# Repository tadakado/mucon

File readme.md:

# 使用上の注意

1. USB-SWDボードを接続する際は、必ず、電源スイッチをオフにして電池を外してください。電源スイッチをオフにしないと 3.3VがBLEモジュール(MDBT50Q)に接続されません。また、ボード間の"V"と"B"の印刷が対応するように接続してください。
2. BLE Micro Pro用に公開されている下記ファームウェアを、独自に書き込んでいます。本キーボードに関して、BLE Micro Pro作者のせきごんさんには問い合わせをしないでください。
    * [BLE Micro Pro Bootloader](https://github.com/sekigon-gonnoc/BLE-Micro-Pro)
    * [QMK for BMP](https://github.com/sekigon-gonnoc/qmk_firmware)
3. キーボード本体右上の穴はキーホルダー用の穴です。ショートの恐れがあるため、金属製リングの使用は避けてください。携帯ストラップなどに使われる紐がお勧めです。同梱のスペーサは携帯ストラップの紐を通す際に、本体、スペーサ、ケースの順に通してください。紐によってケース変形してキーが誤動作するのを防止します。無くしやすいので気をつけてください。

# はじめに

μ'con(もしくはmucon)はキーが5個の5%キーボードです。BLEによるデバイスのメディア操作(音量や再生/停止など)用に設計されています。キーボード本体(メインボード)と各種設定に用いるUSB-SWDボードから成ります。USBはType-Cです。電池はCR2032を使い、BLE Micro Proのファームウェアで、6ヶ月以上動作します。本体重量約4g(電池含まず)。μ'conの名前は、music controller、micro(μ) controller/computer、そしてあるアーティストに由来しています。

# 同梱物

* 本体 x 1個
* USB-SWDボード x 1個
* コンスルー(7pin) x 1個
* TPUケース x 2個
* スペーサ(CT-2002) x 2個 (ストラップをつける際に使用します)

# 初期設定(シンプル)

出荷時の状態から、電池を入れて電源スイッチをオンにすると一台目をペアリングすることができます。
(初期設定(通常)の5.までを実行するとペアリング済みデバイスが消去され出荷時相当になります)

# 初期設定(通常)

1. 電源スイッチをオフにして、つまようじ等で電池を外し、USB-SWDボードを接続して、PC/Macに接続してください。
    * USB-SWDボードの接続は、1.27mmピッチのコンスルーを用います。メインボード上の"V"と"B"の印刷と、USB-SWDボード上の"V"と"B"の印刷が対応するように接続してください。"V"と"B"は、VCCとVBUSのため、逆に接続すると、想定外の電圧がかかり破損の原因となります。
    * 電池ホルダとのショートに気を付けてください。ショート防止のため、USB-SWDボードの裏には絶縁テープが貼ってあります。
    * 

2. PC/MacにUSBケーブルで接続してください。
    * PCの場合、Tera Termで、COM??ポート(ポート番号??はマシンによって異なる)に接続してください。
    * Macの場合、ターミナルで`screen /dev/tty.usbmodem??`を実行します。終了する際は`ctrl-a k`です。
3. BLE Micro ProのCLIのコマンドを使い初期設定をします。
    * `help`コマンドで、BLE Micro ProのCLIのコマンド一覧が出ます。
4. `show`コマンドでペアリング済みのデバイスの一覧が出ます。ペアリング済みのデバイスがある場合は、`del`コマンドで消去してください。
5. デバイス側のペアリング情報も消してください。
6. `adv`コマンドでアドバタイズを開始してください。デバイス側に(BMP)muconが出たらペアリングをしてください。
    * 二台目をペアリングする際は、一台目のデバイスのBlueetoohをオフにしてから、`adv`コマンドを再実行してください。
7. ペアリングが完了したら、USB-SWDボードを取り外し、電池を入れて、電源スイッチをオンにしてください。

# 使用方法

1. 電源スイッチをオンにするとLEDが(電池容量に応じて)1～3回点滅します。最後に少し長く点滅したら接続完了です。
2. キーSWは、左上から反時計回りにSW1～SW5です。
    ```
    SW1   O
    SW2  SW5
    SW3  SW4
    ```
3. デフォルトの設定では、SW1を押しながらSW2を押すと一台目のデバイス、SW1を押しながらSW3を押すと二台目のデバイスに再接続します。
4. SW2が再生/停止、SW3が音量下げる、SW4が音量上げる、SW5は、一回押しが次の曲、二回押しが前の曲です。

# 設定の変更

1. Macでストレージとして認識しない場合(macOS Sonoma以降)は、[シェルスクリプト](macOS/mucon_mount.sh)を使ってマウントしてください。ターミナルで`./mucon_mount.sh mount`を実行します。
2. BLE Micro Proの[ドキュメント](https://sekigon-gonnoc.github.io/BLE-Micro-Pro/#/edit_keymap_file)に従い、
"KEYMAP.JSN"の`"layers":[`の後ろを編集してください。 
3. 設定を変更する際は、PC/Mac上に"KEYMAP.JSN"をコピーして編集後に"mucon"ドライブに戻して(コピーして)ください。
4. 動作がおかしいときは
    * 正しくコピーされているか確認してみてください。ファイルを開いてみるほかに、CLIの`map`コマンドでも確認できます。二回コピーするとうまくいく場合もあります。
    * ファイルの記述にミスがある場合ファイルが正しくコピーされません。デフォルトの"KEYMAP.JSN"でコピーできるか確認してみてください。
    * BLE Micro ProのCLIのコマンド`del`および、デバイス側のペアリング情報を消して、初期設定をしてみてください。
5. ファームウェアのアップデートは、どのような影響があるかわからないため、案内がある場合を除いて行わないでください。
    * アップデートの際は、CLIの`dfu`コマンドにより、dfuモードに移行します。uf2ファイルをドライブにコピーするとアップデートが行われます。
    * また、USBを用いずにSWDでファームウェアを書き込むこともできます。(上級者向け)
    * 書き込んであるファームは、[BLE Micro Pro Bootloader v0.11.0](https://github.com/sekigon-gonnoc/BLE-Micro-Pro/releases/download/v0.11.0/ble_micro_pro_bootloader_0_11_0.uf2)と[QMK for BMP v0.11.2](https://github.com/sekigon-gonnoc/qmk_firmware/releases/download/bmp-0.11.2/ble_micro_pro_default_0_11_2_1.uf2)です。
    * 実験的に[専用ファームウェア](firmware)を用意しました。LEDで接続接続デバイスを確認したり、Musicモードとプレゼンテーションモードを切り替えたりできます。

# ハードウェア

1. 回路図は添付資料(pdfファイル)をご覧ください。"pcb"にはKicadの設計データがあります。
2. BLE Micro Proのファームウェアと、CircutPythonが動くように設計されています。CircuitPythonは消費電力が大きく、電池動作には向いていません。CircuitPythonに関しては資料を参照ください。
3. メインボードにはLEDのほかに、水晶発振子とWS2812C用のパターンがありますが搭載しておりません。水晶発振子はBLE Micro Proのファームウェアでは必須ではないため、また、WS2812Cは省電力化のため外してあります。
4. メインボード裏面には、テスト用のパッドがあります。中央寄りからBOOT, RESET, SWITCH, D2, GNDです。詳細は回路図を参照ください。
5. USB-SWDボードを接続する際は、電源スイッチをオフにして、必ず電池を外してください。電源スイッチをオフにしないと 3.3VがBLEモジュール(MDBT50Q)に接続されません。
6. USB-SWDボードにはUSBの5VからVCCの3.3Vを作るレギュレータがあります。また、μ'con接続用スルーホール(1x7 1.27mm)、SWD(2x5 1.27mm)ピンヘッダ、SWD用スルーホール(1x4 2.54mm)が二つあります。スルーホール径は0.8mm(設計値)です。
7. SWDピンヘッダには、J-LinkやBlack Magic Probeが接続できます。SWD用スルーホールは、ST-LinkV2やBluePill Black Magic Probeの接続用です。SWDによる書き込みは資料を参照ください。
8. BLE Micro Proのファームウェアはマトリックスキーボードを想定しているため、設定ファイルでは、使っていない端子を一つrow_pin(=6,P0.16)に割り当てています。
9. 配線の都合上、P0.05とP0.06がLEDに繋がっていますが、使用するのはP0.05のみです。
10. ケースの設計データ(Fusion360)は"case"にあります。

# デフォルトの設定ファイルの内容

"BMP_config"にファイルがあります。

KEYMAP.JSN
```
{"keyboard":"mucon",
"keymap":"",
"layout":"LAYOUT",
"layers":[
    ["MO(1)", "KC_MPLY", "KC_VOLD","KC_VOLU", "EX(TDD(KC_MNXT,KC_MPRV))"],
    ["KC_TRANS", "ADV_ID0", "ADV_ID1", "KC_NO", "KC_NO"]
]}
```
CONFIG.JSN (編集しない)
```
{"config":{
    "version":2,
    "device_info":{"vid":"0xcafe","pid":"0x9001",
        "name":"mucon","manufacture":"tadakado","description":"A music controller with 5 buttons"},
    "matrix":{"rows":1,"cols":5,"device_rows":1,"device_cols":5,
         "debounce":1,"is_left_hand":1,"diode_direction":0,
         "row_pins":[6],
         "col_pins":[16, 15, 18, 7, 9],
    "layout":[1, 2, 3, 4, 5]},
    "mode":"SINGLE","startup":1,
    "peripheral":{"max_interval":200,"min_interval":100,"slave_latency":0},
    "central":{"max_interval":200,"min_interval":100,"slave_latency":0},
    "led":{"pin":1, "num":1},
    "keymap":{"locale":"JP","use_ascii":0},
    "reserved":[0,20,0,0,0,0,0,0]
}}
```
TAPTERM (編集しない)
```
{"tapping_term":{
	"KC_NO":500
}}
```

# BLE Micro ProのCLI

ドキュメントにはすべてのコマンドの説明が書かれていないようです。CLIの[コード](https://github.com/sekigon-gonnoc/qmk_firmware/blob/dev/ble_micro_pro/tmk_core/protocol/nrf/sdk15/cli.c)やAPIの[コード](https://github.com/sekigon-gonnoc/qmk_firmware/blob/dev/ble_micro_pro/tmk_core/protocol/nrf/sdk15/apidef.h)を参照ください。

# ケース

"case"にFusion360の設計ファイルおよび、3Dプリンタで印刷に用いるstlファイルがあります。TPUでの印刷を想定しています。

# SWDでファームウェアの書き込み方法

(確実なのはJ-Link、安価なのはST-Link V2またはBluePill)

* USBとSWDの両方を接続してください。USBはVCCの3.3Vを作るために使用します。
* J-Linkを用いる場合は、[nRF Connect for Desktop](https://www.nordicsemi.com/Products/Development-tools/nRF-Connect-for-desktop)からProgrammerを起動するとhexファイルが書き込めます。
* Black Magic Probeまたは、BluePill Black Magic Probeを用いる場合は、gdbからhexファイルが書き込めます。
* ST-Link V2を用いる場合には、OpenOCDからhexファイルが書き込めます。
* J-LinkやBlack Magic Probeで使用するSWD(2x5 1.27mm)ピンヘッダを実装しています。ST-Link V2やBluePillを使用する場合は、SWD用スルーホールにピンヘッダを実装して使用してください。干渉を防ぐため、外側のスルーホールを使うことをお勧めします。

## ST-Link V2による書き込み

### ST-Link V2購入先
* [SZ Aitexm Store](https://www.aliexpress.com/item/32792513237.html)、
[Shigezone](https://www.shigezone.com/product/st-link/)

### ST-Link V2をWindows10に認識させる
1. [Zadig](https://zadig.akeo.ie)をダウンロードして実行
2. STM32 STLink => WinUSB

## ST-Link V2とOpenOCDによるNRF52への書き込み
* [参考情報1](https://kunsen.net/2018/09/30/post-1784/)
* [参考情報2](https://4k2.de/microcontroller/openocd-flashing-nrf52/)
1. ソフトのダウンロード
    * [OpenOCD](https://github.com/openocd-org/openocd/releases/download/v0.11.0/openocd-v0.11.0-i686-w64-mingw32.tar.gz)
2. 書き込み
    1. 方法1 コマンドライン
        ```
        bin¥openocd -s share/openocd/scripts -f interface/stlink-v2.cfg -f target/nrf52.cfg -c init -c "reset init" -c halt -c "nrf5 mass_erase" -c “program firmware.hex verify” -c reset -c exit
        ```
    2. 方法2 サーバを起動
        ```
        bin¥openocd -s share/openocd/scripts -f interface/stlink-v2.cfg -f target/nrf52.cfg
        ```
        localhost:4444 にアクセス
        ```
        init
        reset init
        halt
        nrf5 mass_erase
        program firmware.hex verify
        reset
        exit
        ```

## Black Magic Probeによる書き込み

### Black Magic ProbeとgdbによるNRF52への書き込み
* [参考情報1](https://devzone.nordicsemi.com/nordic/nordic-blog/b/blog/posts/flashing-and-debugging-nrf5152-with-a-cheap-blackm)
* [参考情報2](https://developer.arm.com/tools-and-software/open-source-software/developer-tools/gnu-toolchain/downloads-1)
* COMの番号は二つあるうちの一つ目を使う。
* COM番号が大きいとうまく動かないことがあるため、デバイスマネージャーで、表示>表示デバイスの表示として、デバイスのアンインストールで不要なものを削除
    ```
    arm-none-eabi-gdb.exe
    target extended-remote COM4
    monitor swdp_scan
    attach 1
    (monitor erase_mass)
    load firmware.hex
    ```

### Balck Magic Probeとして使えるBluePill Black Magic Probeの作り方(要 ST-Link V2 & BluePill)
* [参考情報](https://jeelabs.org/202x/bmp/)
1. ソフトとデータをダウンロード
    * [ST-Link](https://github.com/stlink-org/stlink/releases/download/v1.7.0/stlink-1.7.0-x86_64-w64-mingw32.zip)
    * [Black Magic Probe](https://github.com/blackmagic-debug/blackmagic/releases/download/v1.7.1/v1.7.1.tar.gz)
2. 必要なファイルをまとめる
    * blackmagic_dfu-swlink.bin
    * blackmagic-swlink.bin
    * st-flash.exe
3. 書き込み
    ```
    st-flash --reset write blackmagic_dfu-swlink.bin 0x8000000
    st-flash --flash=128k write blackmagic-swlink.bin 0x8002000
    ```
* その他の情報
    * Firmwareのスリム化 [参考情報](https://primalcortex.wordpress.com/2017/06/13/building-a-black-magic-debug-probe/)

# BLE Mirco Proファームウェア(uf2)からhexファイルへの変換方法

[参考情報](https://discord.com/channels/376937950409392130/508485002170990602/800355123637125170)

build_BMP_hex.sh
```
#!/bin/sh

mkdir build
cd build

curl -O -L https://github.com/sekigon-gonnoc/BLE-Micro-Pro/releases/download/v0.11.0/ble_micro_pro_bootloader_0_11_0.uf2
curl -O -L https://www.nordicsemi.com/-/media/Software-and-other-downloads/SoftDevices/S140/s140nrf52600.zip
unzip s140nrf52600.zip s140_nrf52_6.0.0_softdevice.hex
curl -O -L https://raw.githubusercontent.com/microsoft/uf2/a690c5a4d9abe393496b3ade88489d39da07b458/utils/uf2conv.py
curl -O -L https://raw.githubusercontent.com/microsoft/uf2/a690c5a4d9abe393496b3ade88489d39da07b458/utils/uf2families.json

dd if=ble_micro_pro_bootloader_0_11_0.uf2 of=BOOTLOADER.uf2 bs=1 count=242688
dd if=ble_micro_pro_bootloader_0_11_0.uf2 of=UICR.uf2 bs=1 skip=242688

python2 uf2conv.py -c -b 0xE0000 -o BOOTLOADER.bin BOOTLOADER.uf2
python2 uf2conv.py -c -b 0x10001000 -o UICR.bin UICR.uf2
objcopy --adjust-vma 0xE0000 -I binary -O ihex BOOTLOADER.bin BOOTLOADER.hex
objcopy --adjust-vma 0x10001000 -I binary -O ihex UICR.bin UICR.hex
```
REGOUT0を3.3Vにする設定(μ'conでは使わない)
```
cat > hex/UICR_REGOUT0_5_3v3.hex << EOF
:020000041000EA
:04130400FDFFFFFFEB
:00000001FF
EOF

unix2dos hex/UICR_REGOUT0_5_3v3.hex
```

# μ'con用CircuitPythonのビルド

"circuitpython"の下にAdafurit_nRF52_BootloaderとCircutPython向けのボード固有のコードがあります。

## Adafurit_nRF52_Bootloaderのビルド
コンパイル環境を構築したら、"circuitpython/boot"にあるファイルを"src/bords"の下に"mucon"を作成してコピーします。
```
make BOARD=mucon
```
で、コンパイルできます。"\_build/build-mucon"にある"\*\_s140\_\*.hex"と"*.uf2"が必要なバイナリです。

## CircuitPythonのビルド
コンパイル環境を構築したら、"circuitpython/ptyhnon"にあるファイルを"ports/nrf/boards"の下に"mucon"フォルダを作成してコピーします。
```
cd ports/nrf ; make V=2 BOARD=mucon
```
で、コンパイルできます。"build-mucon/firmware.uf2"が必要とするバイナリです。
クリスタル未搭載の場合には、"mpconfigboard.h" で`#define BOARD_HAS_32KHZ_XTAL (0)`を設定する必要があります。

### pyファイルのコンパイル(mpyの作成)
pythonのコードをそのまま保存するとサイズが大きくなるため、たくさんのライブラリを使う複雑なプログラムが組めません。そこでライブラリを含めてすべてのpyファイルをコンパイルして小さくします。
circuitpythonをインストールしたフォルダに、["tools/mpy_cross_all.py"](https://github.com/adafruit/circuitpython/blob/main/tools/mpy_cross_all.py)があります。例えば、"py/kmk"にコンパイルしたいpyファイルを置いて、以下を実行すると"mpy/kmk"の下にコンパイルされたmpyファイルができます。
```
python3 mpy_cross_all.py -o mpy/kmk py/kmk
```
なお、circuitpythonの標準ライブラリはmpyファイルとして提供されています。

### CircuitPythonでのCの利用
MicroPytnonにはmpyにCのコードをコンパイルしたバイナリを含めることができるますが、CircuitPythonではその機能は実装されていないため、カスタムモジュールを作りCircuitPython全体をコンパイルする必要があります。[参考情報](https://forums.adafruit.com/viewtopic.php?f=60&t=190383)

### KMKについて
CircuitPythonを利用したBLE HIDキーボードの実装が[KMK](https://github.com/KMKfw/kmk_firmware)です。CircuitPythonのBLE機能を利用しているため、機能が限定されます。また、CircuitPythonでは、スリープモードでの消費電力が大きいため、CRC2032が一日しか持ちません。これらの課題が解決すれば、開発環境として使えます。

# μ'con製造について
一つ一つ手作業で作成しています。Sn-Bi系の低融点ハンダを使用しているので、もし修理等をされる場合は半田ごてやヒートガンの温度設定に注意してください。リフローは160～180度、ヒートガンは160度、半田ごては270度(実測または設定値)で作業しています。

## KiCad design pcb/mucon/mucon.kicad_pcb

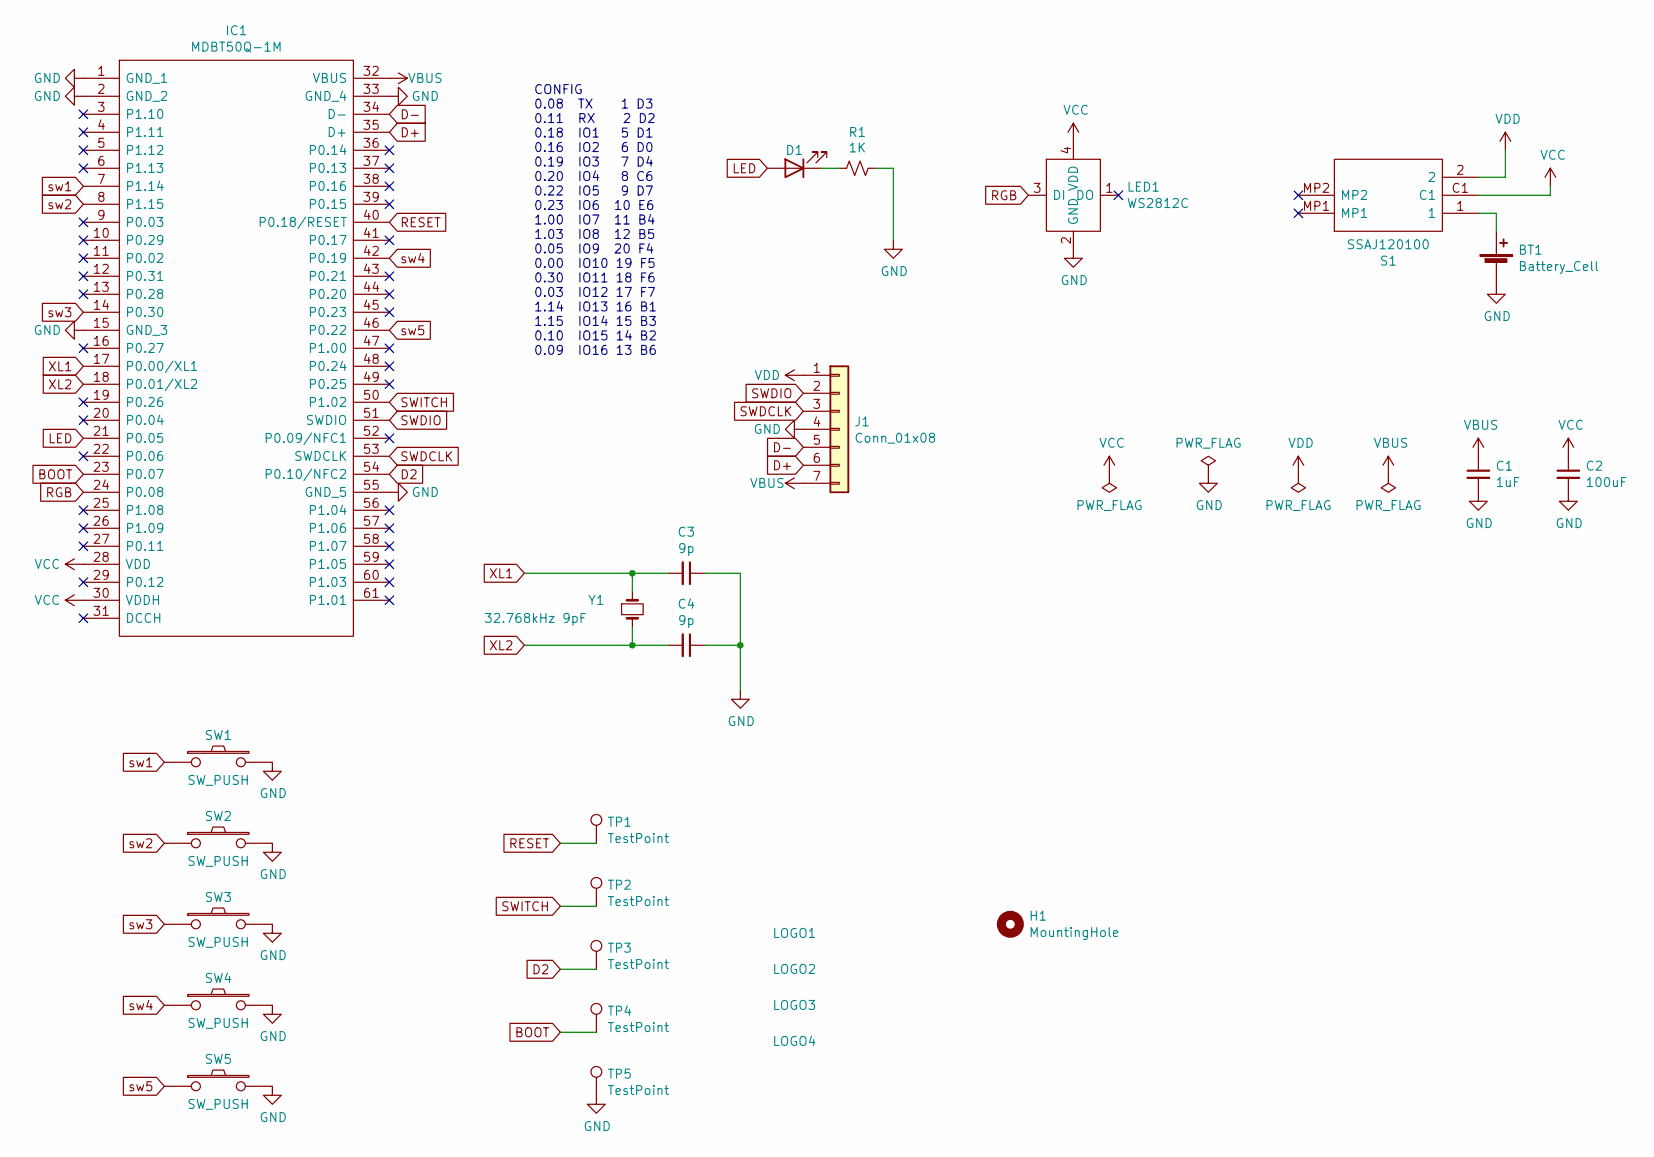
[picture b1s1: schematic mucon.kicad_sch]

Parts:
BT1: Battery_Cell; BK888_mod6
C1: 1uF; C_0603_1608Metric
C2: 100uF; C_1206_3216Metric
C3, C4: 9p; C_0402_1005Metric
D1: LED; LED_0603_1608Metric
H1: MountingHole; MountingHole_2.2mm_M2
IC1: MDBT50Q-1M; Manufacturer_Part_Number 113990582
J1: Conn_01x08; PinHeader_1x07_P1.27mm_Vertical
LED1: WS2812C; WS2812C2020; Manufacturer_Part_Number WS2812C-2020
LOGO1: Logo; mucon
LOGO2: Logo; mucon2
LOGO3: Logo; quarter_note3
LOGO4: Logo; star_3mm
R1: 1K; R_0603_1608Metric
S1: SSAJ120100; Manufacturer_Part_Number SSAJ120100
SW1, SW2, SW3, SW4, SW5: SW_PUSH; SKRPABE010
TP1, TP2, TP3, TP4, TP5: TestPoint; TestPoint_Pad_D1.0mm
Y1: 32.768kHz 9pF; CM9VT1A

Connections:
BOOT: IC1.23 (P0.07), TP4.1
D2: IC1.54 (P0.10/NFC2), TP3.1
D+: IC1.35 (D+), J1.6
D-: IC1.34 (D-), J1.5
GND: BT1.2 (-), C1.2, C2.2, C3.1, C4.1, IC1.1 (GND_1), IC1.2 (GND_2), IC1.15 (GND_3), IC1.33 (GND_4), IC1.55 (GND_5), J1.4, LED1.2 (GND), R1.1, SW1.2, SW2.2, SW3.2, SW4.2, SW5.2, TP5.1
LED: D1.2 (A), IC1.21 (P0.05)
unnamed: BT1.1 (+), S1.1
unnamed: D1.1 (K), R1.2
RESET: IC1.40 (P0.18/RESET), TP1.1
RGB: IC1.24 (P0.08), LED1.3 (DI)
SWDCLK: IC1.53 (SWDCLK), J1.3
SWDIO: IC1.51 (SWDIO), J1.2
SWITCH: IC1.50 (P1.02), TP2.1
VBUS: C1.1, IC1.32 (VBUS), J1.7
VCC: C2.1, IC1.28 (VDD), IC1.30 (VDDH), LED1.4 (VDD), S1.C1
VDD: J1.1, S1.2
XL1: C3.2, IC1.17 (P0.00/XL1), Y1.1
XL2: C4.2, IC1.18 (P0.01/XL2), Y1.2
sw1: IC1.7 (P1.14), SW1.1
sw2: IC1.8 (P1.15), SW2.1
sw3: IC1.14 (P0.30), SW3.1
sw4: IC1.42 (P0.19), SW4.1
sw5: IC1.46 (P0.22), SW5.1

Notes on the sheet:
CONFIG 0.08 TX 1 D3 0.11 RX 2 D2 0.18 IO1 5 D1 0.16 IO2 6 D0 0.19 IO3 7 D4 0.20 IO4 8 C6 0.22 IO5 9 D7 0.23 IO6 10 E6 1.00 IO7 11 B4 1.03 IO8 12 B5 0.05 IO9 20 F4 0.00 IO10 19 F5 0.30 IO11 18 F6 0.03 IO12 17 F7 1.14 IO13 16 B1 1.15 IO14 15 B3 0.10 IO15 14 B2 0.09 IO16 13 B6

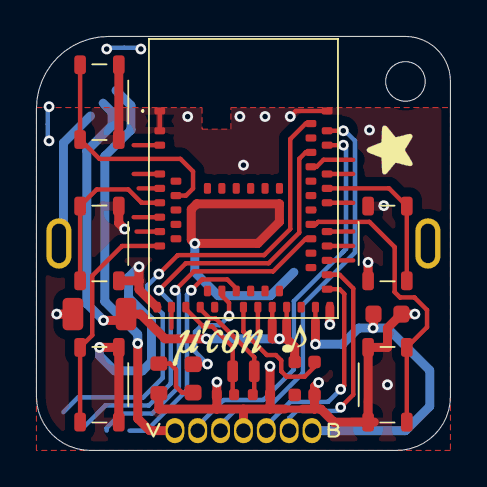
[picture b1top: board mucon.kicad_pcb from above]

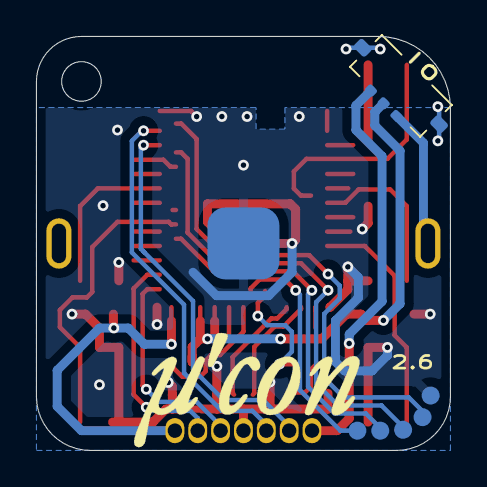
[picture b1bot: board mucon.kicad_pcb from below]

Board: 2 copper layers, 23.0 x 23.0 mm, 27 parts (8 on the bottom side), 23 nets.

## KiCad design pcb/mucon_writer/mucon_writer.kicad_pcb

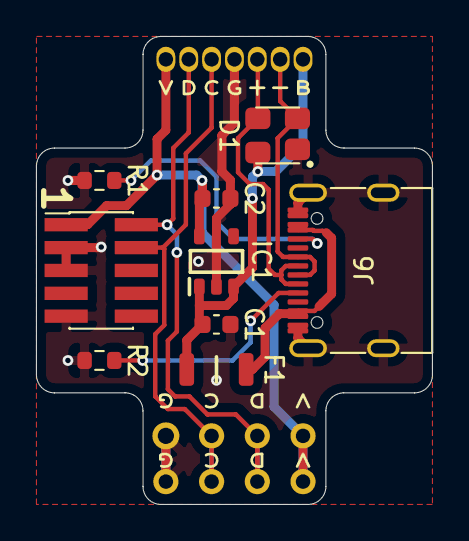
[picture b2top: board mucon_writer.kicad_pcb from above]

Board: 2 copper layers, 22.0 x 26.0 mm, 12 parts (0 on the bottom side), 10 nets.

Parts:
C1: 0.1uF; C_0603_1608Metric
C2: 1uF; C_0603_1608Metric
D1: PRTR5V0U2X; SOT-143
F1: MF-NSMF050-2; FUSC3216X85N
IC1: NJM2866F33-TE1; SOT95P280X130-5N
J1: Conn_01x07; PinHeader_1x07_P1.27mm_Vertical
J2, J3: Conn_01x04; PinHeader_1x04_P2.54mm_Vertical
J4: Conn_02x05_Top_Bottom; PinHeader_2x05_P1.27mm_Vertical_SMD
J6: USB_C_Receptacle_USB2.0; USB_C_Receptacle_5077CR-16-SMC2
R1, R2: 5.1K; R_0603_1608Metric

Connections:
CLK: J1.3, J2.3, J3.3, J4.4
D+: D1.2, J1.6, J6.A6, J6.B6
D-: D1.3, J1.5, J6.A7, J6.B7
GND: C1.2, C2.2, D1.1, IC1.2, J1.4, J2.4, J3.4, J4.3, J4.5, J4.9, J6.A1, J6.A12, J6.B1, J6.B12, J6.S1, R1.2, R2.2
unnamed: F1.1, J6.A4, J6.A9, J6.B4, J6.B9
unnamed: J6.A5, R2.1
unnamed: J6.B5, R1.1
SWIO: J1.2, J2.2, J3.2, J4.2
VBUS: C1.1, D1.4, F1.2, IC1.1, IC1.3, J1.7
VCC: C2.1, IC1.5, J1.1, J2.1, J3.1, J4.1

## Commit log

2022-05-04 initial
2022-05-04 add case information and stl file (gcode file is removed)
2022-05-06 add a picture
2022-05-11 raised dot
2022-07-23 change capacitor (from 1uF to 100uF), PCB design files are in KiCad6 format
2022-07-23 remove unused file
2022-11-03 custom firmware
2023-02-23 Update battery life information
2023-04-05 supress warnings
2023-07-15 update custom firmware description
